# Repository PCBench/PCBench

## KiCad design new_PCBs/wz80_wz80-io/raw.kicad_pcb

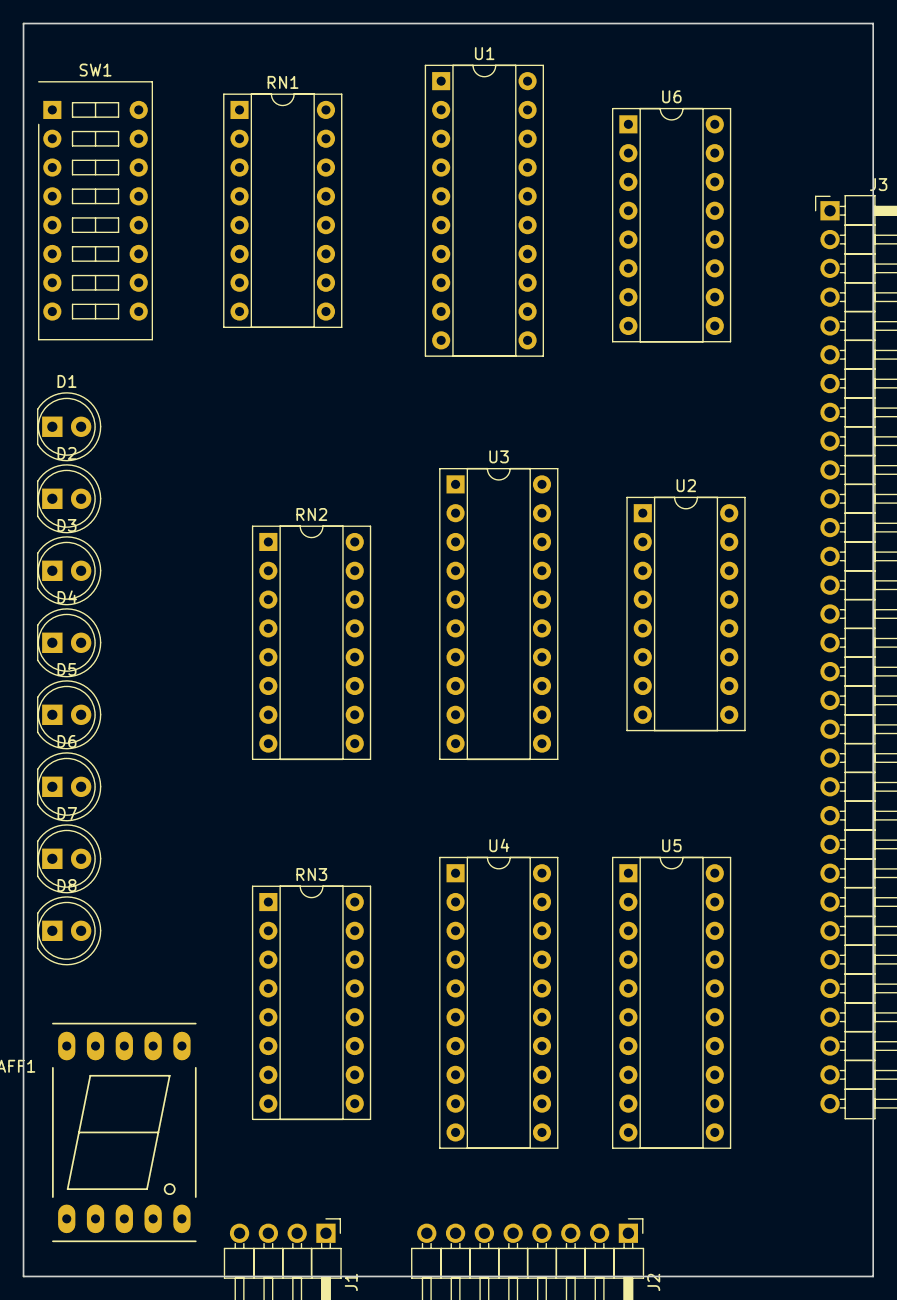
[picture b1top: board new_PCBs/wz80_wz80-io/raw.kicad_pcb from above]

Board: 2 copper layers, 74.9 x 110.5 mm, 22 parts (0 on the bottom side), 71 nets, no tracks yet.

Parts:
AFF1: LTS-6980HR; 7SegmentLED_LTS6760_LTS6780
D1, D2, D3, D4, D5, D6, D7, D8: LED; LED_D5.0mm
J1: CONN_01X04; Pin_Header_Angled_1x04_Pitch2.54mm
J2: CONN_01X08; Pin_Header_Angled_1x08_Pitch2.54mm
J3: CONN_01X32; Pin_Header_Angled_1x32_Pitch2.54mm
RN1, RN2, RN3: R_Pack08; DIP-16_W7.62mm_Socket
SW1: SW_DIP_x08; SW_DIP_x8_W7.62mm_Slide
U1: 74LS245; DIP-20_W7.62mm_Socket
U2: 74LS595; DIP-16_W7.62mm_Socket
U3, U4, U5: 74LS374; DIP-20_W7.62mm_Socket
U6: 74LS138; DIP-16_W7.62mm_Socket

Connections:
/D0: J3.24, U1.18, U2.15, U3.3, U4.3, U5.3
/D1: J3.23, U1.17, U2.1, U3.4, U4.4, U5.4
/D2: J3.22, U1.16, U2.2, U3.7, U4.7, U5.7
/D3: J3.21, U1.15, U2.3, U3.8, U4.8, U5.8
/D4: J3.20, U1.14, U2.4, U3.13, U4.13, U5.13
/D5: J3.19, U1.13, U2.5, U3.14, U4.14, U5.14
/D6: J3.18, U1.12, U2.6, U3.17, U4.17, U5.17
/D7: J3.17, U1.11, U2.7, U3.18, U4.18, U5.18
/S0: AFF1.7, RN3.1
/S1: AFF1.6, RN3.2
/S2: AFF1.4, RN3.3
/S3: AFF1.2, RN3.4
/S4: AFF1.1, RN3.5
/S5: AFF1.9, RN3.6
/S6: AFF1.10, RN3.7
/S7: AFF1.5, RN3.8
GND: AFF1.3, AFF1.8, D1.1, D2.1, D3.1, D4.1, D5.1, D6.1, D7.1, D8.1, J1.2, J3.26, RN1.1, RN1.2, RN1.3, RN1.4, RN1.5, RN1.6, RN1.7, RN1.8, U1.10, U2.8, U3.1, U3.10, U4.1, U4.10, U5.1, U5.10, U6.8
unnamed: D1.2, RN2.1
unnamed: D2.2, RN2.2
unnamed: D3.2, RN2.3
unnamed: D4.2, RN2.4
unnamed: D5.2, RN2.5
unnamed: D6.2, RN2.6
unnamed: D7.2, RN2.7
unnamed: D8.2, RN2.8
unnamed: J1.1, U2.12, U2.13, U6.14
unnamed: J1.3, U2.11
unnamed: J1.4, U2.14
unnamed: J2.1, U5.19
unnamed: J2.2, U5.16
unnamed: J2.3, U5.15
unnamed: J2.4, U5.12
unnamed: J2.5, U5.9
unnamed: J2.6, U5.6
unnamed: J2.7, U5.5
unnamed: J2.8, U5.2
unnamed: J3.9, U6.5
unnamed: J3.15, U6.2
unnamed: J3.16, U6.1
unnamed: J3.28, U6.6
unnamed: J3.30, U6.3
unnamed: J3.32, U6.4
unnamed: RN1.9, SW1.9, U1.9
unnamed: RN1.10, SW1.10, U1.8
unnamed: RN1.11, SW1.11, U1.7
unnamed: RN1.12, SW1.12, U1.6
unnamed: RN1.13, SW1.13, U1.5
unnamed: RN1.14, SW1.14, U1.4
unnamed: RN1.15, SW1.15, U1.3
unnamed: RN1.16, SW1.16, U1.2
unnamed: RN2.9, U3.2
unnamed: RN2.10, U3.5
unnamed: RN2.11, U3.6
unnamed: RN2.12, U3.9
unnamed: RN2.13, U3.12
unnamed: RN2.14, U3.15
unnamed: RN2.15, U3.16
unnamed: RN2.16, U3.19
unnamed: RN3.9, U4.19
unnamed: RN3.10, U4.16
unnamed: RN3.11, U4.15
unnamed: RN3.12, U4.12
unnamed: RN3.13, U4.9
unnamed: RN3.14, U4.6
unnamed: RN3.15, U4.5
unnamed: RN3.16, U4.2
unnamed: U1.19, U6.15
unnamed: U3.11, U6.11
unnamed: U4.11, U6.10
unnamed: U5.11, U6.9
VCC: J3.25, SW1.1, SW1.2, SW1.3, SW1.4, SW1.5, SW1.6, SW1.7, SW1.8, U1.1, U1.20, U2.16, U3.20, U4.20, U5.20, U6.16

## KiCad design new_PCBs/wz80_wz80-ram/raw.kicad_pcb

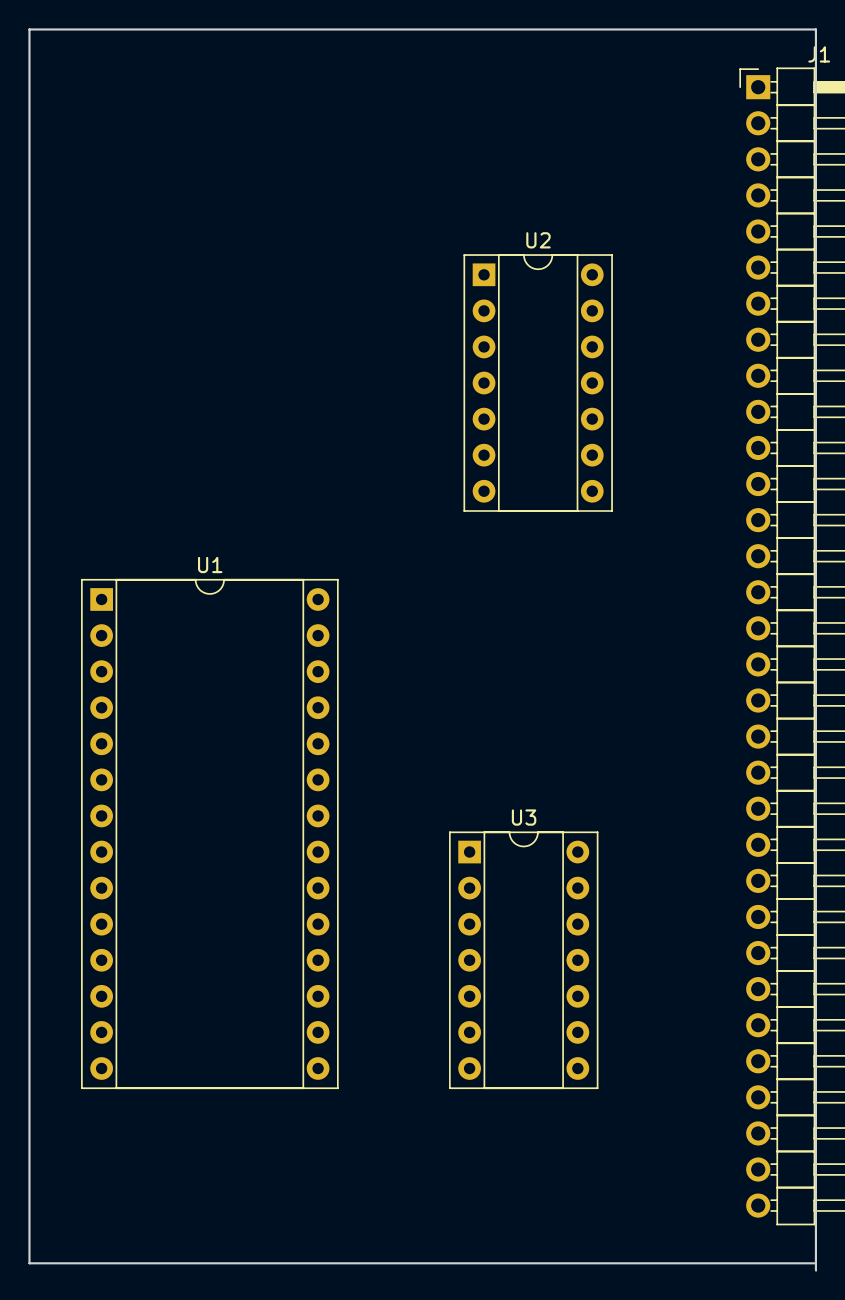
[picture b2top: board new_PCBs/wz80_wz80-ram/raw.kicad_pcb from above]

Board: 2 copper layers, 55.4 x 87.4 mm, 4 parts (0 on the bottom side), 32 nets, no tracks yet.

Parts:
J1: CONN_01X32; Pin_Header_Angled_1x32_Pitch2.54mm
U1: HM62256BLP-7; DIP-28_W15.24mm_Socket
U2: 74LS32; DIP-14_W7.62mm_Socket
U3: 74HC04; DIP-14_W7.62mm_Socket

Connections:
/A0: J1.16, U1.10
/A1: J1.15, U1.9
/A2: J1.14, U1.8
/A3: J1.13, U1.7
/A4: J1.12, U1.6
/A5: J1.11, U1.5
/A6: J1.10, U1.4
/A7: J1.9, U1.3
/A8: J1.8, U1.25
/A9: J1.7, U1.24
/A10: J1.6, U1.21
/A11: J1.5, U1.23
/A12: J1.4, U1.2
/A13: J1.3, U1.26
/A14: J1.2, U1.1
/A15: J1.1, U3.1
/D0: J1.24, U1.11
/D1: J1.23, U1.12
/D2: J1.22, U1.13
/D3: J1.21, U1.15
/D4: J1.20, U1.16
/D5: J1.19, U1.17
/D6: J1.18, U1.18
/D7: J1.17, U1.19
GND: J1.26, U1.14, U2.7, U3.7
unnamed: J1.29, U2.1
unnamed: J1.30, U2.5
unnamed: J1.31, U2.2, U2.4
unnamed: U1.20, U3.2
unnamed: U1.22, U2.6
unnamed: U1.27, U2.3
VCC: J1.25, U1.28, U2.14, U3.14

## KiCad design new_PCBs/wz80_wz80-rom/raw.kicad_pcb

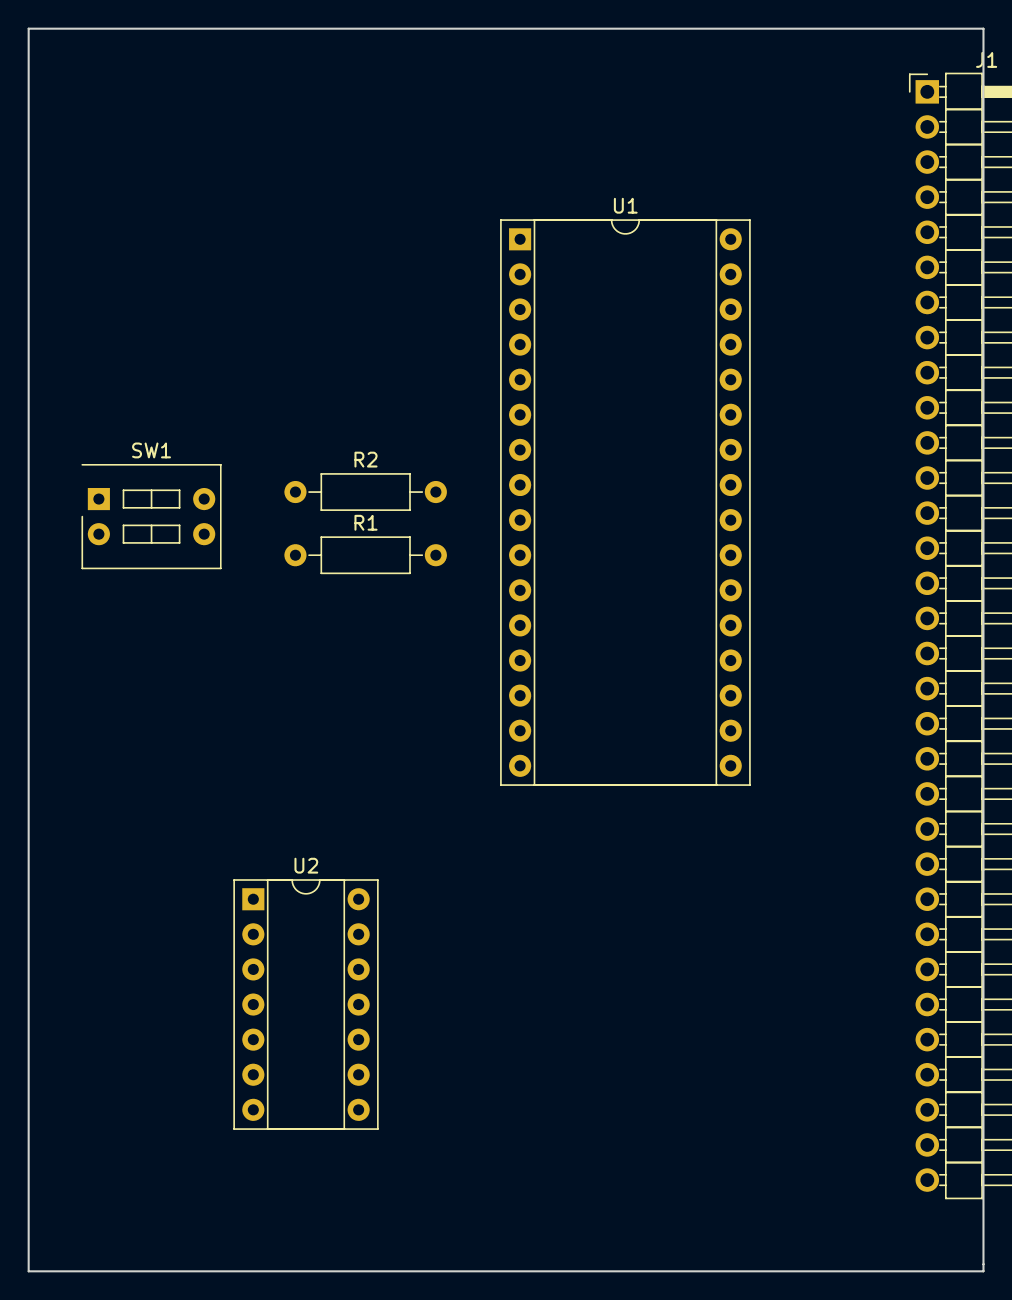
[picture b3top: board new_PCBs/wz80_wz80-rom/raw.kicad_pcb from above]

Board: 2 copper layers, 69.1 x 89.9 mm, 6 parts (0 on the bottom side), 30 nets, no tracks yet.

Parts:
J1: CONN_01X32; Pin_Header_Angled_1x32_Pitch2.54mm
R1, R2: R; R_Axial_DIN0207_L6.3mm_D2.5mm_P10.16mm_Horizontal
SW1: SW_DIP_x02; SW_DIP_x2_W7.62mm_Slide
U1: SST39SF010; DIP-32_W15.24mm_Socket
U2: 74LS32; DIP-14_W7.62mm_Socket

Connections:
/A0: J1.16, U1.12
/A1: J1.15, U1.11
/A2: J1.14, U1.10
/A3: J1.13, U1.9
/A4: J1.12, U1.8
/A5: J1.11, U1.7
/A6: J1.10, U1.6
/A7: J1.9, U1.5
/A8: J1.8, U1.27
/A9: J1.7, U1.26
/A10: J1.6, U1.23
/A11: J1.5, U1.25
/A12: J1.4, U1.4
/A13: J1.3, U1.28
/A14: J1.2, U1.29
/A15: J1.1, R2.1, SW1.4, U1.3, U1.22
/A16: R1.1, SW1.3, U1.2
/D0: J1.24, U1.13
/D1: J1.23, U1.14
/D2: J1.22, U1.15
/D3: J1.21, U1.17
/D4: J1.20, U1.18
/D5: J1.19, U1.19
/D6: J1.18, U1.20
/D7: J1.17, U1.21
/MREQ: J1.31, U2.4
/RD: J1.30, U2.5
GND: J1.26, R1.2, R2.2, U1.16, U2.7
unnamed: U1.24, U2.6
VCC: J1.25, SW1.1, SW1.2, U1.31, U1.32, U2.14

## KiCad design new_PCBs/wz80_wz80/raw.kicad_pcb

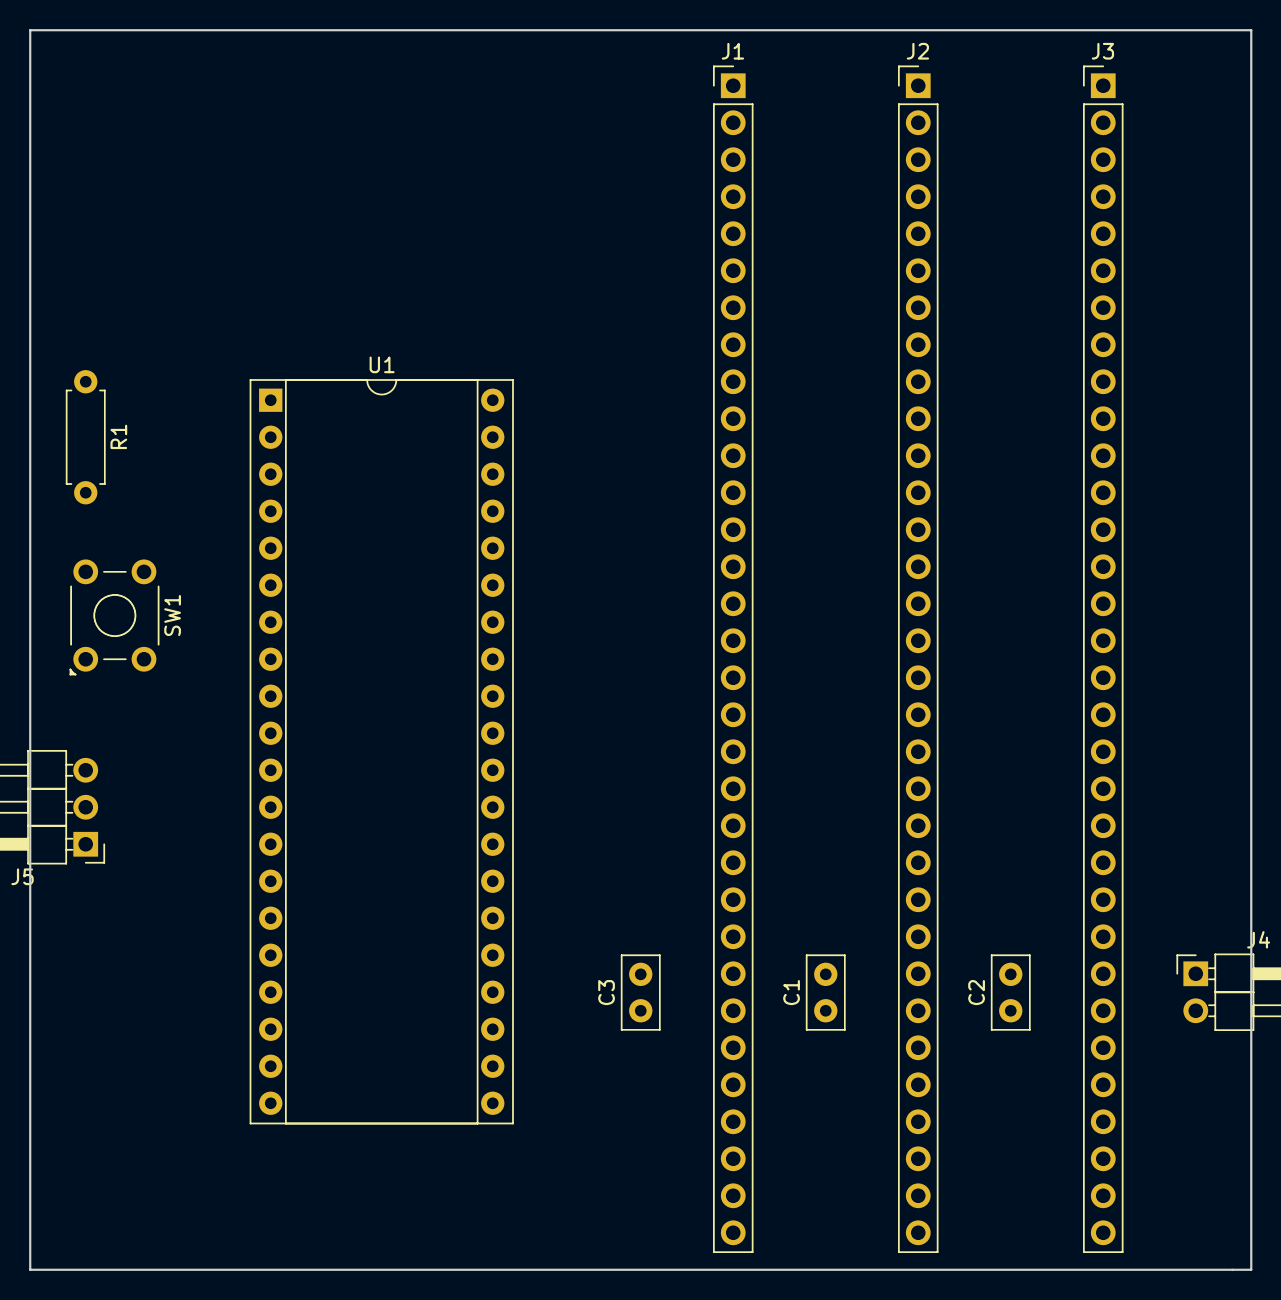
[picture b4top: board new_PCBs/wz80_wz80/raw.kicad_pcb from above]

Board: 2 copper layers, 83.8 x 85.1 mm, 11 parts (0 on the bottom side), 33 nets, no tracks yet.

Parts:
C1, C2, C3: 100nF; C_Disc_D5.0mm_W2.5mm_P2.50mm
J1, J2, J3: CONN_01X32; Socket_Strip_Straight_1x32_Pitch2.54mm
J4: CONN_01X02; Pin_Header_Angled_1x02_Pitch2.54mm
J5: CONN_01X03; Pin_Header_Angled_1x03_Pitch2.54mm
R1: 2K2; R_Axial_DIN0207_L6.3mm_D2.5mm_P7.62mm_Horizontal
SW1: SW_Push_Dual; SW_TH_Tactile_Omron_B3F-10xx
U1: Z80CPU; DIP-40_W15.24mm_Socket

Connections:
/A0: J1.16, J2.16, J3.16, U1.30
/A1: J1.15, J2.15, J3.15, U1.31
/A2: J1.14, J2.14, J3.14, U1.32
/A3: J1.13, J2.13, J3.13, U1.33
/A4: J1.12, J2.12, J3.12, U1.34
/A5: J1.11, J2.11, J3.11, U1.35
/A6: J1.10, J2.10, J3.10, U1.36
/A7: J1.9, J2.9, J3.9, U1.37
/A8: J1.8, J2.8, J3.8, U1.38
/A9: J1.7, J2.7, J3.7, U1.39
/A10: J1.6, J2.6, J3.6, U1.40
/A11: J1.5, J2.5, J3.5, U1.1
/A12: J1.4, J2.4, J3.4, U1.2
/A13: J1.3, J2.3, J3.3, U1.3
/A14: J1.2, J2.2, J3.2, U1.4
/A15: J1.1, J2.1, J3.1, U1.5
/CLK: J1.27, J2.27, J3.27, J5.2, U1.6
/D0: J1.24, J2.24, J3.24, U1.14
/D1: J1.23, J2.23, J3.23, U1.15
/D2: J1.22, J2.22, J3.22, U1.12
/D3: J1.21, J2.21, J3.21, U1.8
/D4: J1.20, J2.20, J3.20, U1.7
/D5: J1.19, J2.19, J3.19, U1.9
/D6: J1.18, J2.18, J3.18, U1.10
/D7: J1.17, J2.17, J3.17, U1.13
/IORQ: J1.32, J2.32, J3.32, U1.20
/M1: J1.28, J2.28, J3.28, U1.27
/MREQ: J1.31, J2.31, J3.31, U1.19
/RD: J1.30, J2.30, J3.30, U1.21
/WR: J1.29, J2.29, J3.29, U1.22
GND: C1.2, C2.2, C3.2, J1.25, J2.25, J3.25, J4.1, J5.1, SW1.1, SW1.3, U1.29
unnamed: R1.2, SW1.2, SW1.4, U1.26
VCC: C1.1, C2.1, C3.1, J1.26, J2.26, J3.26, J4.2, J5.3, R1.1, U1.11, U1.16, U1.17, U1.24, U1.25

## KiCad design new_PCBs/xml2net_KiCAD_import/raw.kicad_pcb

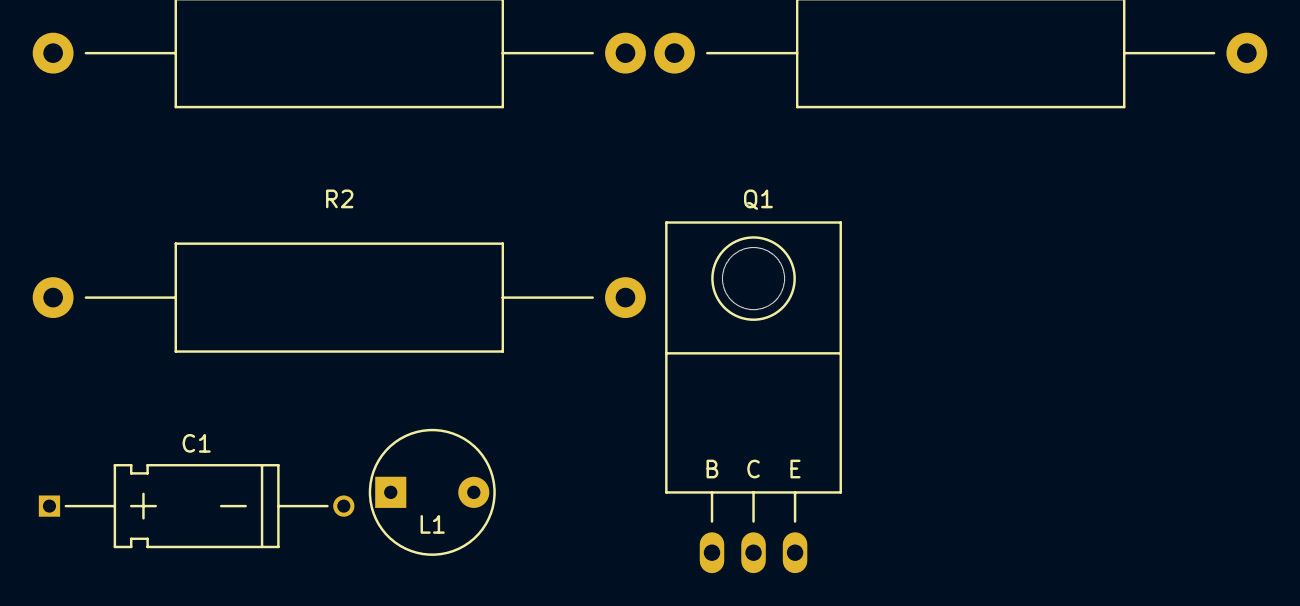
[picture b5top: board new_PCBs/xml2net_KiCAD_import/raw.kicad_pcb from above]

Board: 2 copper layers, 6 parts (0 on the bottom side), 5 nets, no tracks yet.

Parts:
C1: Ceramic_Capacitor; C_Axial_D5_L11_P18
L1: Inductor; INDUCTOR_V
Q1: NPN-Transistor; TO-220_Bipolar-BCE_Horizontal-KS
R1: 220Ω_Resistor; Resistor_Cement_Horizontal_Meggitt-SBC-2
R2: 400Ω_Resistor; Resistor_Cement_Horizontal_Meggitt-SBC-2
R3: 100Ω_Resistor; Resistor_Cement_Horizontal_Meggitt-SBC-2

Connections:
unnamed: R1.1, R2.2, R3.1
unnamed: Q1.2, R1.2
unnamed: C1.1, L1.1, Q1.3
unnamed: Q1.1, R2.1
unnamed: C1.2, L1.2, R3.2

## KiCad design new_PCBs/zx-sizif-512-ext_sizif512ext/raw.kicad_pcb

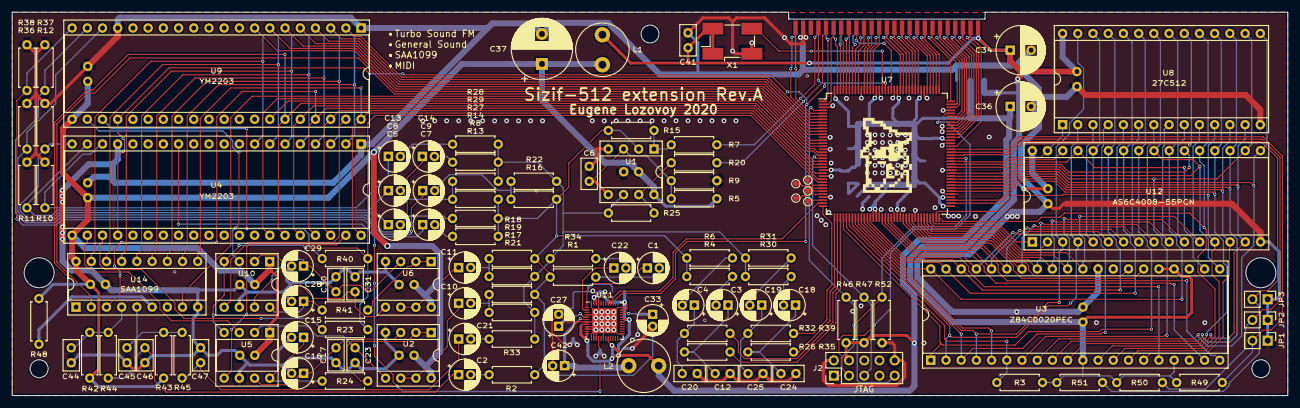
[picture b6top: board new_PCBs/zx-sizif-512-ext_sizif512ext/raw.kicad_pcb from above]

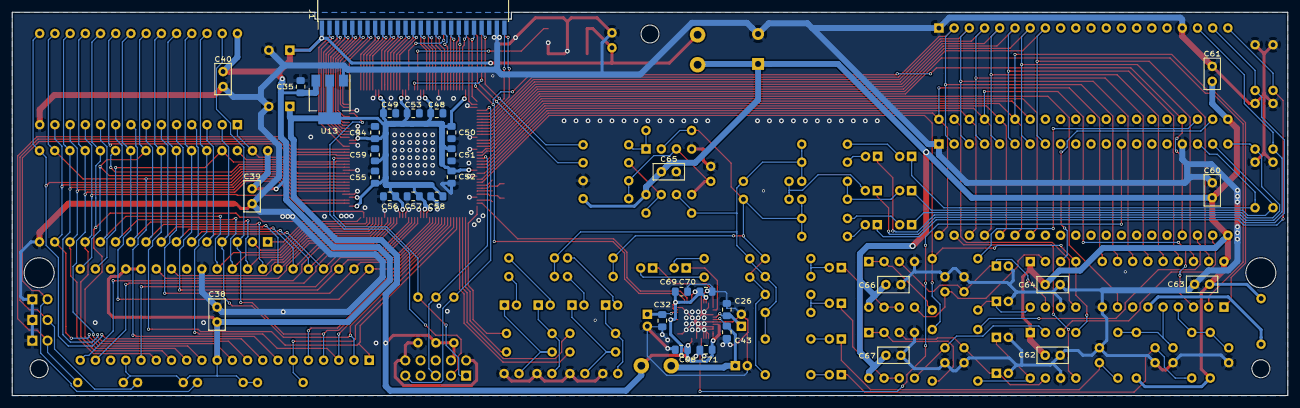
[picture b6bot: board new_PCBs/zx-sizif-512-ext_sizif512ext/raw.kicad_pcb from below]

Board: 2 copper layers, 213.0 x 64.0 mm, 156 parts (33 on the bottom side), 179 nets.

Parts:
C1, C2, C3, C4, C5, C7, C8, C9, C10, C11, C13, C14, C15, C16, C18, C19, C21, C22, C27, C28, C29, C33: 10u/16V; CP_Radial_D5.0mm_P2.00mm
C6, C17, C30, C38, C39, C40, C41, C60, C61, C62, C63, C64, C65, C66, C67: 100n; C_Disc_D5.0mm_W2.5mm_P2.50mm
C12, C20, C24, C25: 1n; C_Disc_D5.0mm_W2.5mm_P2.50mm
C23, C31: 2.2n; C_Disc_D5.0mm_W2.5mm_P2.50mm
C26, C32, C35, C43, C48, C49, C50, C51, C52, C53, C54, C55, C56, C57, C58, C59, C68, C69, C70, C71: 100n; C_0805_2012Metric_Pad1.15x1.40mm_HandSolder
C34, C36: 220u/16V; CP_Radial_D8.0mm_P3.50mm
C37: 470u/16V; CP_Radial_D10.0mm_P5.00mm
C42: 47u/16V; CP_Radial_D5.0mm_P2.00mm
C44, C45, C46, C47: 10n; C_Disc_D5.0mm_W2.5mm_P2.50mm
H1, H2: MountingHole; MountingHole_5mm_7mm_fence
H3, H4, H5: MountingHole; MountingHole_3mm
J1: Conn_02x25_Odd_Even; PinHeader_2x25_P1.27mm_Edge_SMD
J2: PinHeader; PinHeader_2x05_P2.54mm_Vertical
JP1, JP2, JP3: Jumper / Pin header 1x2 Pitch=2.54mm; PinHeader_1x02_P2.54mm_Vertical
L1: 220u/1A; L_Radial_D8.7mm_P5.00mm_Fastron_07HCP
L2: 220u/0.2A; L_Radial_D8.7mm_P5.00mm_Fastron_07HCP
LOGO1: graphic; black-mage2
R1, R4, R6, R8, R13, R17, R18, R19, R21, R28, R29, R30, R31, R34: 24k; R_Axial_DIN0207_L6.3mm_D2.5mm_P7.62mm_Horizontal
R2, R15, R25, R33, R46, R47, R48, R49, R50, R51, R52: 10k; R_Axial_DIN0207_L6.3mm_D2.5mm_P7.62mm_Horizontal
R3, R26, R32, R35, R39: 2k; R_Axial_DIN0207_L6.3mm_D2.5mm_P7.62mm_Horizontal
R5, R14, R16, R22, R27: 47k; R_Axial_DIN0207_L6.3mm_D2.5mm_P7.62mm_Horizontal
R7, R20: 2.2k; R_Axial_DIN0207_L6.3mm_D2.5mm_P7.62mm_Horizontal
R9: 27k; R_Axial_DIN0207_L6.3mm_D2.5mm_P7.62mm_Horizontal
R10, R11, R12, R36, R37, R38: 3.3k; R_Axial_DIN0207_L6.3mm_D2.5mm_P7.62mm_Horizontal
R23, R40, R42, R43, R44, R45: 1k; R_Axial_DIN0207_L6.3mm_D2.5mm_P7.62mm_Horizontal
R24, R41: 470; R_Axial_DIN0207_L6.3mm_D2.5mm_P7.62mm_Horizontal
TP1, TP2, TP3, TP4, TP5: TestPoint; TestPoint_Pad_D1.0mm
U1, U2, U6: MCP602; DIP-8_W7.62mm_Socket
U3: Z84C0020PEC; DIP-40_W15.24mm_Socket
U4, U9: YM2203; DIP-40_W15.24mm_Socket
U5, U10: YM3014B; DIP-8_W7.62mm_Socket
U7: EPM3256ATC144; TQFP-144_20x20mm_P0.5mm
U8: 27C512; DIP-28_W15.24mm_Socket
U11: SAM2695; QFN-48-1EP_6x6mm_P0.4mm_EP4.2x4.2mm
U12: AS6C4008-55PCN; DIP-32_W15.24mm_Socket
U13: AMS1117-3.3; SOT-223-3_TabPin2
U14: SAA1099; DIP-18_W7.62mm_Socket
X1: 32MHz; Oscillator_SMD_EuroQuartz_XO91-4Pin_7.0x5.0mm_HandSoldering

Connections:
+3.3VA: C42.1, C43.1, L2.2, U11.6
+3V3: C36.1, C48.1, C49.1, C50.1, C51.1, C52.1, C53.1, C54.1, C55.1, C56.1, C57.1, C58.1, C59.1, C68.1, C69.1, C70.1, C71.1, J2.4, L2.1, R46.2, R47.2, U7.24, U7.50, U7.51, U7.58, U7.73, U7.76, U7.95, U7.115, U7.123, U7.130, U7.144, U11.8, U11.11, U11.12, U11.20, U11.31, U11.35, U11.41, U11.46, U11.47, U13.2
+5V: C34.1, C35.2, C38.2, C39.2, C40.2, C41.2, J1.1, J1.2, L1.1, R3.1, R49.1, R50.1, R51.1, U3.11, U3.17, U3.24, U3.25, U8.28, U12.32, U13.3, X1.1, X1.4
+5VA: C37.1, C60.2, C61.2, C62.2, C63.2, C64.2, C65.2, C66.2, C67.2, L1.2, R5.2, R42.2, R43.2, R48.2, U1.8, U2.8, U4.21, U5.1, U6.8, U9.21, U10.1, U14.18
/A0: J1.35, U7.140
/A1: J1.33, U7.138
/A2: J1.32, U7.136
/A3: J1.31, U7.137
/A4: J1.30, U7.133
/A5: J1.36, U7.139
/A6: J1.29, U7.134
/A7: J1.28, U7.131
/A8: J1.6, U7.97
/A9: J1.9, U7.102
/A10: J1.11, U7.106
/A11: J1.10, U7.101
/A12: J1.8, U7.99
/A13: J1.20, U7.113
/A14: J1.24, U7.119
/A15: J1.23, U7.120
/AA0: U4.37, U7.23, U9.37, U14.3
/AD0: U4.40, U7.27, U9.40, U14.10
/AD1: U4.2, U7.7, U9.2, U14.11
/AD2: U4.3, U7.8, U9.3, U14.12
/AD3: U4.4, U7.9, U9.4, U14.13
/AD4: U4.5, U7.10, U9.5, U14.14
/AD5: U4.6, U7.11, U9.6, U14.15
/AD6: U4.7, U7.12, U9.7, U14.16
/AD7: U4.8, U7.14, U9.8, U14.17
/AY_A1: C5.1, R12.2, U4.20
/AY_A2: C7.1, R38.2, U9.20
/AY_B1: C8.1, R11.2, U4.19
/AY_B2: C9.1, R37.2, U9.19
/AY_C1: C13.1, R10.2, U4.18
/AY_C2: C14.1, R36.2, U9.18
/BUS0: J1.49, U7.5
/BUS1: J1.50, U7.6
/CFG0: JP1.2, R49.2, U7.92
/CFG1: JP2.2, R50.2, U7.91
/CFG2: JP3.2, R51.2, U7.90
/CLK32: U7.128, X1.3
/CLKCPU: J1.34, U7.125
/D0: J1.37, U7.142
/D1: J1.38, U7.141
/D2: J1.39, U7.143
/D3: J1.22, U7.117
/D4: J1.21, U7.118
/D5: J1.18, U7.111
/D6: J1.16, U7.109
/D7: J1.14, U7.107
/FM1: C10.1, U2.6, U2.7
/FM2: C11.1, U6.6, U6.7
/FM_ENA: R23.2, R40.2, U5.4, U7.28, U10.4
/GA0: U3.30, U7.68, U8.10, U12.12
/GA1: U3.31, U7.67, U8.9, U12.11
/GA2: U3.32, U7.66, U8.8, U12.10
/GA3: U3.33, U7.65, U8.7, U12.9
/GA4: U3.34, U7.62, U8.6, U12.8
/GA5: U3.35, U7.60, U8.5, U12.7
/GA6: U3.36, U7.55, U8.4, U12.6
/GA7: U3.37, U7.53, U8.3, U12.5
/GA8: U3.38, U7.48, U8.25, U12.27
/GA9: U3.39, U7.47, U8.24, U12.26
/GA10: U3.40, U7.46, U8.21, U12.23
/GA11: U3.1, U7.40, U8.23, U12.25
/GA12: U3.2, U7.42, U8.2, U12.4
/GA13: U3.3, U7.43, U8.26, U12.28
/GA14: U3.4, U7.44, U8.27, U12.3
/GA15: U3.5, U7.45
/GCH0: C3.1, C12.1, R26.1
/GCH1: C4.1, C20.1, R32.1
/GCH2: C18.1, C24.1, R35.1
/GCH3: C19.1, C25.1, R39.1
/GCLK: R3.2, U3.6, U7.41
/GD0: U3.14, U7.71, U8.11, U12.13
/GD1: U3.15, U7.75, U8.12, U12.14
/GD2: U3.12, U7.79, U8.13, U12.15
/GD3: U3.8, U7.80, U8.15, U12.17
/GD4: U3.7, U7.81, U8.16, U12.18
/GD5: U3.9, U7.78, U8.17, U12.19
/GD6: U3.10, U7.74, U8.18, U12.20
/GD7: U3.13, U7.72, U8.19, U12.21
/GDAC0: R26.2, U7.39
/GDAC1: R32.2, U7.38
/GDAC2: R35.2, U7.37
/GDAC3: R39.2, U7.36
/GMA15: U7.87, U8.1, U12.31
/GMA16: U7.69, U12.2
/GMA17: U7.70, U12.1
/GMA18: U7.86, U12.30
/MIDI_CLK: U7.35, U11.39
/MIDI_IN: U4.13, U11.16
/MIDI_L: C1.1, U11.1
/MIDI_R: C22.1, U11.2
/MIX_L: J1.43, R7.1
/MIX_R: J1.42, R20.1
/SAA_CLK: U7.16, U14.8
/SAA_L: C2.1, C46.1, R44.2
/SAA_R: C21.1, C47.1, R45.2
/TCK: J2.1, R52.1, U7.89
/TDI: J2.9, R46.1, U7.4
/TDO: J2.3, U7.104
/TMS: J2.5, R47.1, U7.20
/YM_M: U4.38, U7.25, U9.38
/~ARD: U4.36, U7.22, U9.36
/~AWR: U4.35, U7.21, U9.35, U14.1
/~BUSACK: J1.3, U7.96
/~BUSRQ: J1.5, U7.98
/~GINT: U3.16, U7.49
/~GIORQ: U3.20, U7.56
/~GM1: U3.27, U7.63
/~GMREQ: U3.19, U7.54
/~GRAM: U7.83, U12.22
/~GRD: U3.21, U7.82, U8.22, U12.24
/~GRESET: U3.26, U7.61
/~GROM: U7.88, U8.20
/~GWR: U3.22, U7.84, U12.29
/~HALT: J1.4, U7.93
/~INT: J1.40, U7.2
/~IORQ: J1.13, U7.108
/~IORQGE: J1.19, U7.116
/~M1: J1.25, U7.122
/~MREQ: J1.27, U7.132
/~NMI: J1.41, U7.1
/~RD: J1.17, U7.112
/~RFSH: J1.26, U7.121
/~ROMCSB: J1.12, U7.103
/~RST: J1.44, U4.24, U7.127, U9.24, U11.38
/~SAA_CS: U7.15, U14.2
/~WAIT: J1.7, U7.100
/~WR: J1.15, U7.110
/~YM1_CS: U4.34, U7.18
/~YM2_CS: U7.19, U9.34
GND: C6.1, C12.2, C15.2, C16.2, C17.2, C20.2, C23.2, C24.2, C25.2, C26.2, C27.2, C28.2, C29.2, C30.2, C31.2, C32.2, C33.2, C34.2, C35.1, C36.2, C37.2, C38.1, C39.1, C40.1, C41.1, C42.2, C43.2, C44.2, C45.2, C46.2, C47.2, C48.2, C49.2, C50.2, C51.2, C52.2, C53.2, C54.2, C55.2, C56.2, C57.2, C58.2, C59.2, C60.1, C61.1, C62.1, C63.1, C64.1, C65.1, C66.1, C67.1, C68.2, C69.2, C70.2, C71.2, J1.47, J1.48, J2.2, J2.10, JP1.1, JP2.1, JP3.1, R9.2, R10.1, R11.1, R12.1, R36.1, R37.1, R38.1, R52.2, U1.4, U2.4, U3.29, U4.1, U4.17, U5.6, U6.4, U7.3, U7.13, U7.17, U7.26, U7.33, U7.52, U7.57, U7.59, U7.64, U7.77, U7.85, U7.94, U7.105, U7.114, U7.124, U7.129, U7.135, U8.14, U9.1, U9.17, U10.6, U11.4, U11.7, U11.9, U11.10, U11.13, U11.14, U11.15, U11.18, U11.25, U11.36, U11.45, U11.48, U11.49, U12.16, U13.1, U14.9, X1.2
unnamed: C1.2, R1.2
unnamed: C2.2, R2.2
unnamed: C3.2, R4.2
unnamed: C4.2, R6.2
unnamed: C5.2, R8.2
unnamed: C6.2, R5.1, R9.1, U1.3, U1.5
unnamed: C7.2, R13.2
unnamed: C8.2, R14.2, R27.2
unnamed: C9.2, R16.2, R22.2
unnamed: C10.2, R17.2, R21.2
unnamed: C11.2, R18.2, R19.2
unnamed: C13.2, R28.2
unnamed: C14.2, R29.2
unnamed: C15.1, R24.2, U5.8
unnamed: C16.1, C17.1, U2.3, U5.7
unnamed: C18.2, R30.2
unnamed: C19.2, R31.2
unnamed: C21.2, R33.2
unnamed: C22.2, R34.2
unnamed: C23.1, U2.5, U5.2
unnamed: C26.1, C27.1, U11.5
unnamed: C28.1, R41.2, U10.8
unnamed: C29.1, C30.1, U6.3, U10.7
unnamed: C31.1, U6.5, U10.2
unnamed: C32.1, C33.1, U11.34
unnamed: C44.1, R42.1, R44.1, U14.4
unnamed: C45.1, R43.1, R45.1, U14.5
unnamed: R1.1, R2.1, R4.1, R6.1, R8.1, R13.1, R14.1, R15.1, R16.1, R17.1, R18.1, U1.2
unnamed: R7.2, R15.2, U1.1
unnamed: R19.1, R21.1, R22.1, R25.1, R27.1, R28.1, R29.1, R30.1, R31.1, R33.1, R34.1, U1.6
unnamed: R20.2, R25.2, U1.7
unnamed: R23.1, U4.23
unnamed: R24.1, U2.1, U2.2
unnamed: R40.1, U9.23
unnamed: R41.1, U6.1, U6.2
unnamed: R48.1, U14.6
unnamed: TP1.1, U7.29
unnamed: TP2.1, U7.30
unnamed: TP3.1, U7.31
unnamed: TP4.1, U7.32
unnamed: TP5.1, U7.34
unnamed: U4.22, U5.3
unnamed: U4.39, U5.5
unnamed: U9.22, U10.3
unnamed: U9.39, U10.5

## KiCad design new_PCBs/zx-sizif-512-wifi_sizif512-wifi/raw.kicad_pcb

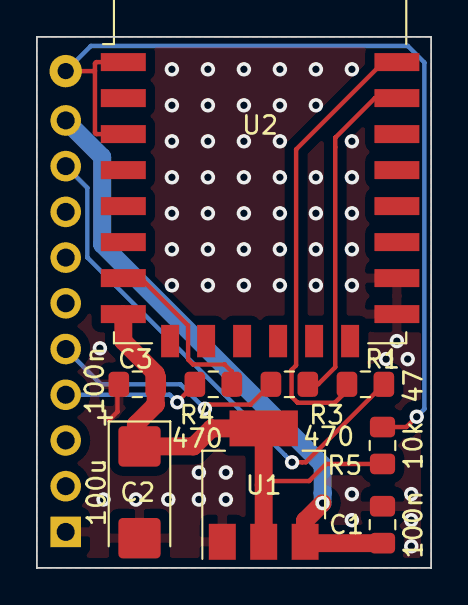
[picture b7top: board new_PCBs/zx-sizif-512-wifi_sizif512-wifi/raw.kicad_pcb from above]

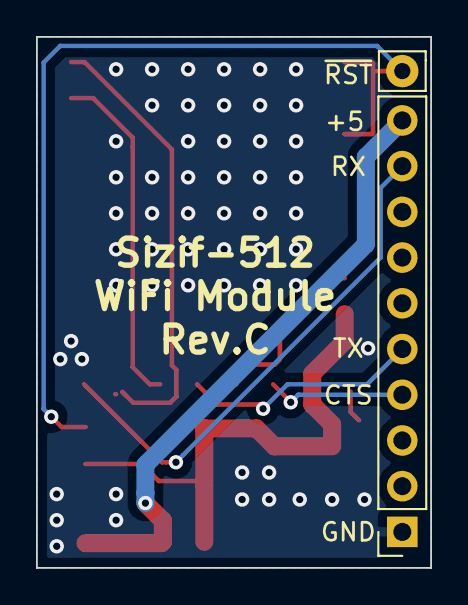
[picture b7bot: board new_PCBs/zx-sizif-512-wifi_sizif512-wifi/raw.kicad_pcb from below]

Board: 2 copper layers, 21.9 x 29.5 mm, 11 parts (2 on the bottom side), 10 nets.

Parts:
C1, C3: 100n; C_0805_2012Metric_Pad1.15x1.40mm_HandSolder
C2: 100u; CP_EIA-6032-15_Kemet-U_Pad2.25x2.35mm_HandSolder
J1: Conn_01x10; PinSocket_1x10_P2.54mm_Vertical
R1: 47; C_0805_2012Metric_Pad1.15x1.40mm_HandSolder
R3, R4: 470; C_0805_2012Metric_Pad1.15x1.40mm_HandSolder
R5: 10k; C_0805_2012Metric_Pad1.15x1.40mm_HandSolder
TP1: TestPoint; Pin_D0.9mm_L10.0mm_W2.4mm_FlatFork
U1: AMS1117-3.3; SOT-223-3_TabPin2
U2: ESP-12E

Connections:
+3V3: C2.1, C3.1, R5.2, U1.2, U2.8
+5V: C1.1, J1.10, U1.3
CTS: J1.4, R4.2
GND: C1.2, C2.2, C3.2, J1.1, U1.1, U2.15, U2.16
unnamed: R1.1, U2.22
unnamed: R3.1, U2.21
unnamed: R4.1, U2.7
unnamed: R5.1, TP1.1, U2.1, U2.3
RX: J1.9, R1.2
TX: J1.5, R3.2
